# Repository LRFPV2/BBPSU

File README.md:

# BBPSU

The Better Breadboard Power SUpply is an alternative to the cheap Chinese knockoff breadboard power supplies. Features: USB-C power input SMD PTC resettable fuse support Large direct-solder power input pads THT pad for power LED or capacitor 20 2.54mm pins for rock-solid connection to the breadboard

I originally designed this for a 16-bit CPU project to tackle the problem of power distribution over a large amount of breadboards (15+). This little PCB turned out to work fantastically and I'm quite happy with the results so far. Next steps would to make the Vcc/Gnd connections configurable based on different breadboards and add a cooler logo. Also, I would like to use the high-power USB-C connectors, rather than the data version.

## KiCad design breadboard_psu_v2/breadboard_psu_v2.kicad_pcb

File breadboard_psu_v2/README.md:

# BBPSU
The Better Breadboard Power SUpply is an alternative to the cheap Chinese knockoff breadboard power supplies.
Features:
USB-C power input
SMD PTC resettable fuse support
Large direct-solder power input pads
THT pad for power LED or capacitor
20 2.54mm pins for rock-solid connection to the breadboard

I originally designed this for a 16-bit CPU project to tackle the problem of power distribution over a large amount of breadboards (15+). This little PCB turned out to work fantastically and I'm quite happy with the results so far.
Next steps would to make the Vcc/Gnd connections configurable based on different breadboards and add a cooler logo. Also, I would like to use the high-power USB-C connectors, rather than the data version.

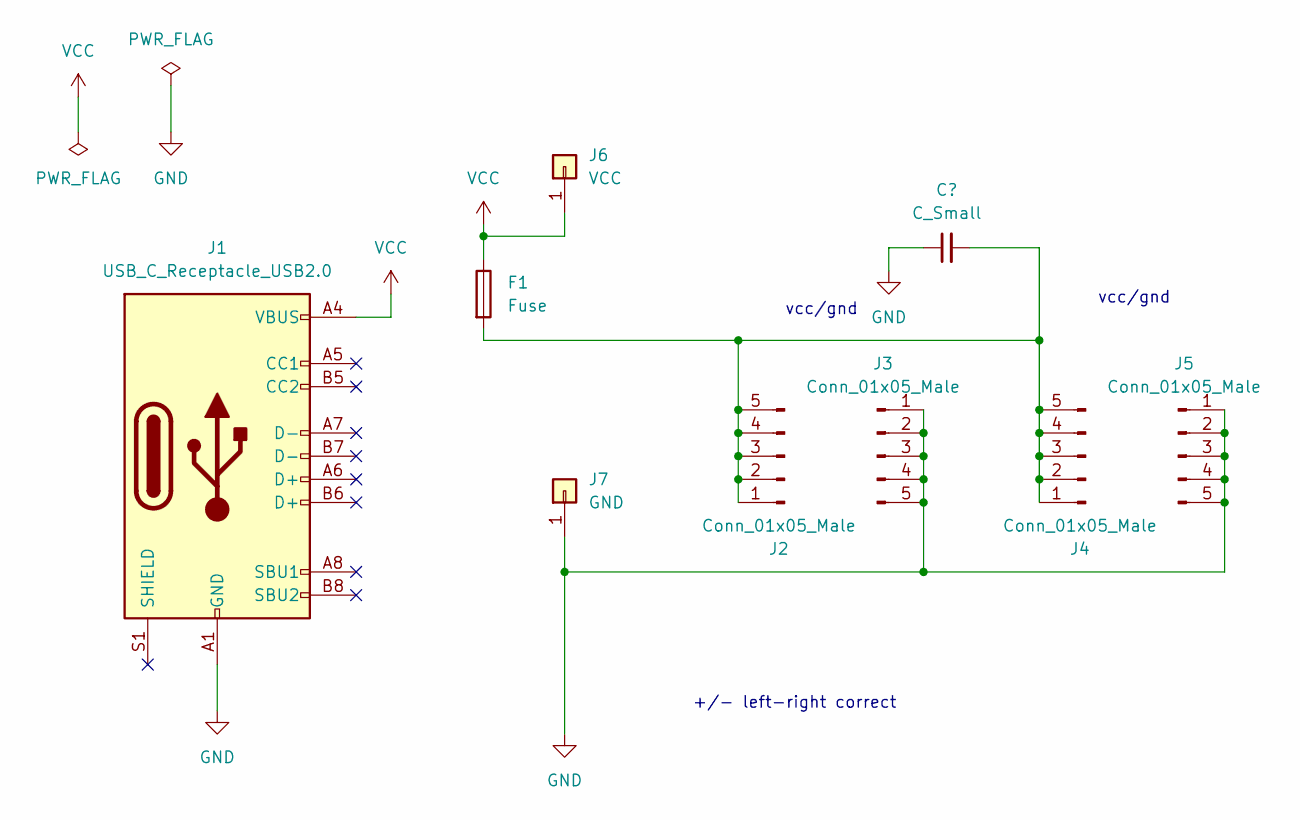
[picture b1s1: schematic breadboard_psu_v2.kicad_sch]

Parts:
F1: Fuse; Fuse_1812_4532Metric_Pad1.30x3.40mm_HandSolder
J1: USB_C_Receptacle_USB2.0; USB_C_Receptacle_HRO_TYPE-C-31-M-12
J2, J3, J4, J5: Conn_01x05_Male; PinHeader_1x05_P2.54mm_Vertical
J6: VCC; 5mm_pad
J7: GND; 5mm_pad

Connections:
GND: J1.A1 (GND), J1.A12 (GND), J1.B1 (GND), J1.B12 (GND), J3.1, J3.2, J3.3, J3.4, J3.5, J5.1, J5.2, J5.3, J5.4, J5.5, J7.1; also elsewhere on the board
unnamed 1: F1.2, J2.1, J2.2, J2.3, J2.4, J2.5, J4.1, J4.2, J4.3, J4.4, J4.5; also elsewhere on the board
VCC: F1.1, J1.A4 (VBUS), J1.A9 (VBUS), J1.B4 (VBUS), J1.B9 (VBUS), J6.1

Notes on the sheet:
vcc/gnd
+/- left-right correct

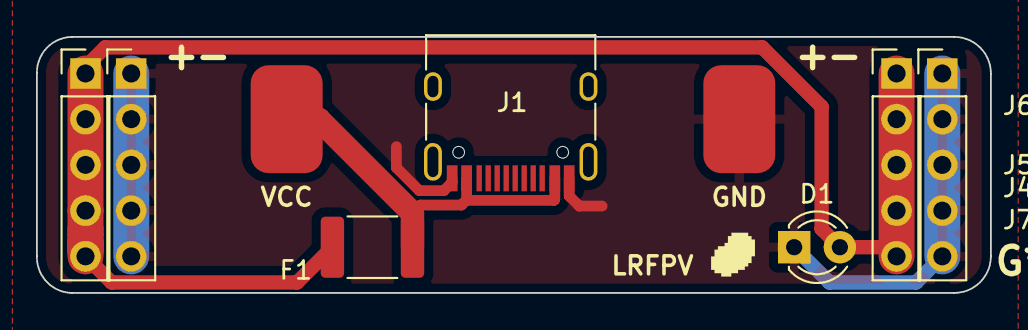
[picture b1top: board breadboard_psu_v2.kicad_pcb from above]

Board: 2 copper layers, 53.0 x 14.2 mm, 9 parts (0 on the bottom side), 3 nets.

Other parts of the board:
D1: LED; LED_D3.0mm

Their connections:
GND: D1.1 (K); also elsewhere on the board
unnamed 1: D1.2 (A); also elsewhere on the board

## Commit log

2022-07-19 Add files via upload
    V2
